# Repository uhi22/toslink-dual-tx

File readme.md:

# TOSLINK dual Transmitter

Converts two digital lines to optical (e.g. data and clock).

## Features

- allows inverting the clock signal
- optional chip select input for gating the clock
- if just straight-through signals are needed, omit the logic ICs and close the solder jumper for direct feed-through

## Specifications

- Optical transmitters: 2× Toshiba TOTX173 (6 Mb/s max)
- Supply: 8–18V, on-board L7805 5V regulator
- Logic: 74HC86 (clock invert), 74HC00 (clock gating via CS)

Made with KiCad version 9.

[Schematic (PDF)](toslink_dual_tx.pdf)

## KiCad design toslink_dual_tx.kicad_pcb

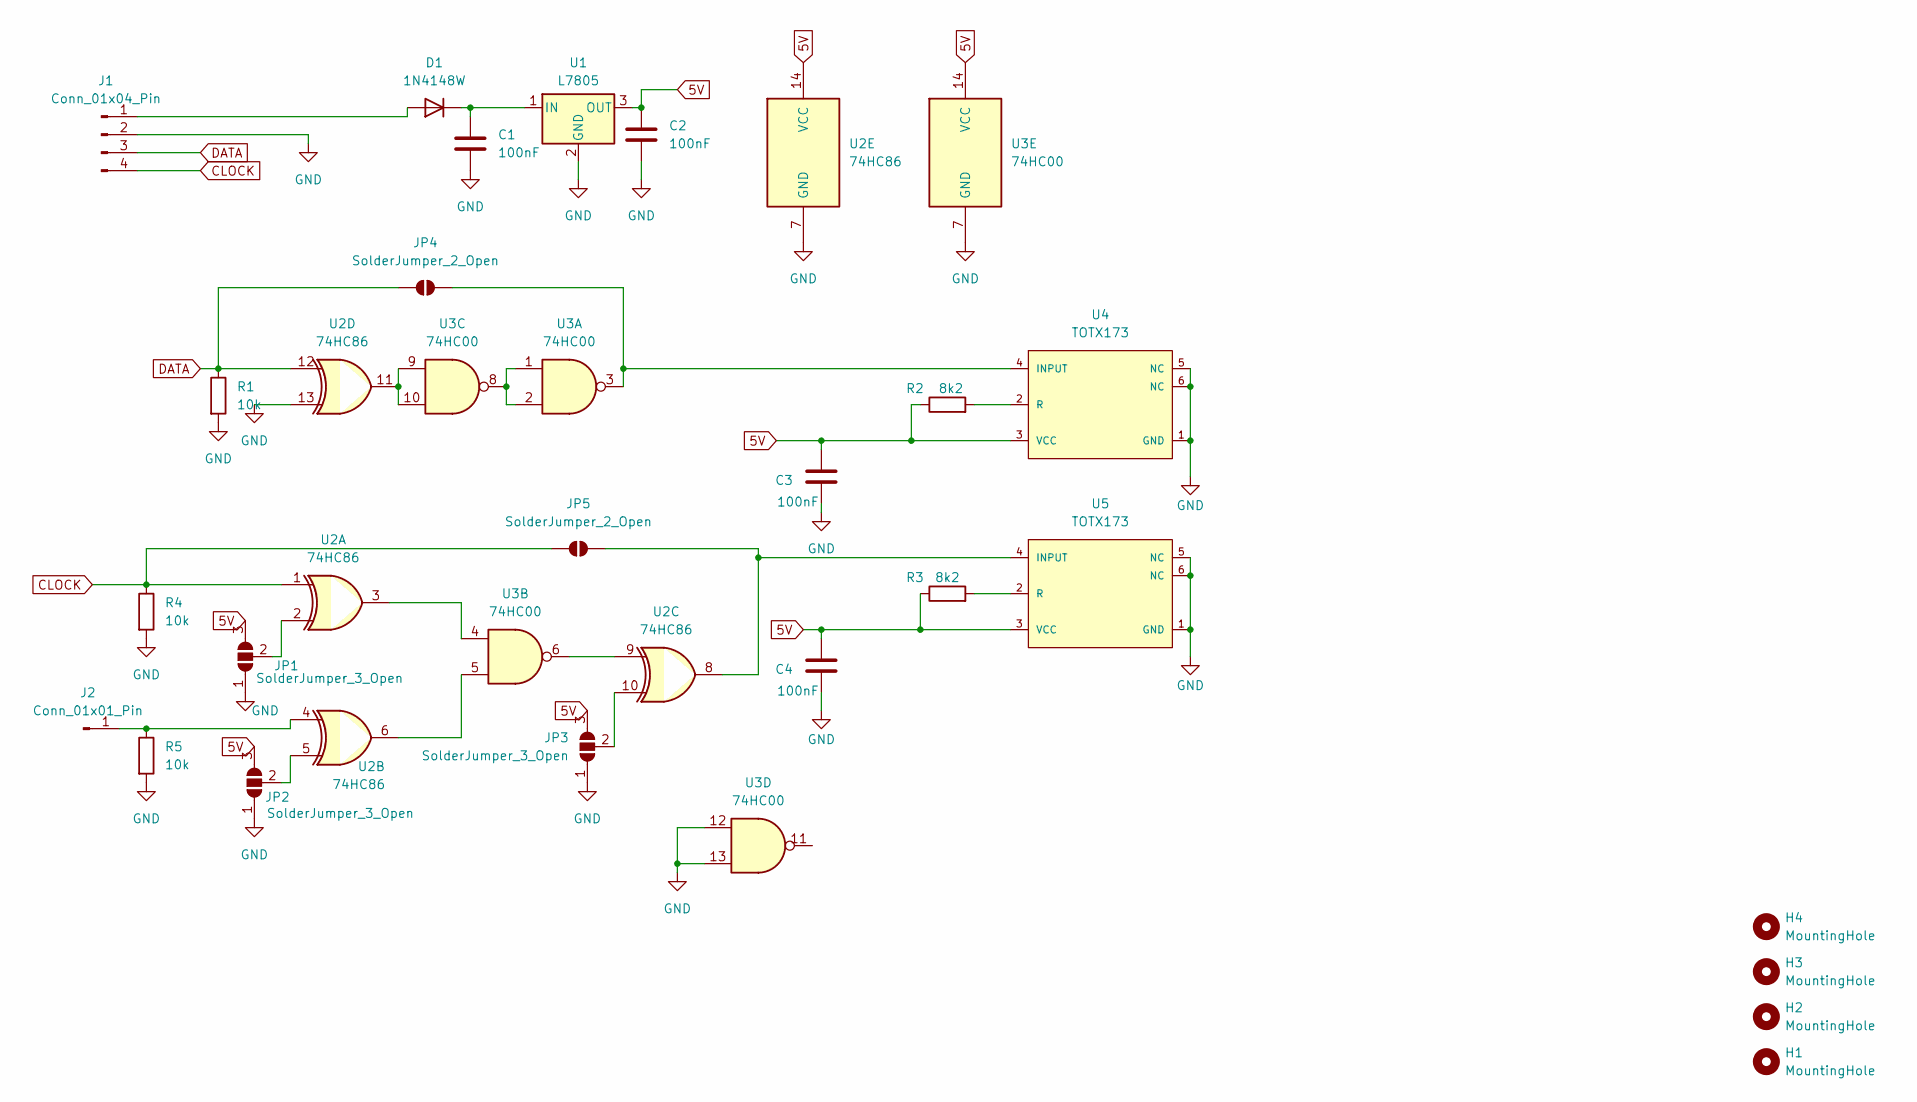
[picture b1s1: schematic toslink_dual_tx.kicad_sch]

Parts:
C1, C2, C3, C4: 100nF; C_0805_2012Metric_Pad1.18x1.45mm_HandSolder
D1: 1N4148W; D_SOD-123
H1, H2, H3, H4: MountingHole; MountingHole_3.2mm_M3
J1: Conn_01x04_Pin; PinHeader_1x04_P2.54mm_Vertical
J2: Conn_01x01_Pin; PinHeader_1x01_P2.54mm_Vertical
JP1, JP2, JP3: SolderJumper_3_Open; SolderJumper-3_P1.3mm_Open_RoundedPad1.0x1.5mm_NumberLabels
JP4, JP5: SolderJumper_2_Open; SolderJumper-2_P1.3mm_Open_Pad1.0x1.5mm
R1, R4, R5: 10k; R_0805_2012Metric_Pad1.20x1.40mm_HandSolder
R2, R3: 8k2; R_0805_2012Metric_Pad1.20x1.40mm_HandSolder
U1: L7805; TO-252-2
U2: 74HC86; SO-14_5.3x10.2mm_P1.27mm
U3: 74HC00; SO-14_5.3x10.2mm_P1.27mm
U4, U5: TOTX173; Toshiba_TOTX170_TOTX173_TOTX193_TOTX194

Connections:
5V: C2.1, C3.1, C4.1, JP1.3 (B), JP2.3 (B), JP3.3 (B), R2.1, R3.1, U1.3 (OUT), U2.14 (VCC), U3.14 (VCC), U4.3 (VCC), U5.3 (VCC)
CLOCK: J1.4, JP5.1 (A), R4.1, U2.1
DATA: J1.3, JP4.1 (A), R1.1, U2.12
GND: C1.2, C2.2, C3.2, C4.2, J1.2, JP1.1 (A), JP2.1 (A), JP3.1 (A), R1.2, R4.2, R5.2, U1.2 (GND), U2.7 (GND), U2.13, U3.7 (GND), U3.12, U3.13, U4.1 (GND), U4.5 (NC), U4.6 (NC), U5.1 (GND), U5.5 (NC), U5.6 (NC)
unnamed: D1.2 (A), J1.1
unnamed: C1.1, D1.1 (K), U1.1 (IN)
unnamed: J2.1, R5.1, U2.4
unnamed: JP1.2 (C), U2.2
unnamed: JP2.2 (C), U2.5
unnamed: JP3.2 (C), U2.10
unnamed: JP4.2 (B), U3.3, U4.4 (INPUT)
unnamed: JP5.2 (B), U2.8, U5.4 (INPUT)
unnamed: U2.3, U3.4
unnamed: U2.6, U3.5
unnamed: U2.9, U3.6
unnamed: U2.11, U3.9, U3.10
unnamed: U3.1, U3.2, U3.8
unnamed: R2.2, U4.2 (R)
unnamed: R3.2, U5.2 (R)

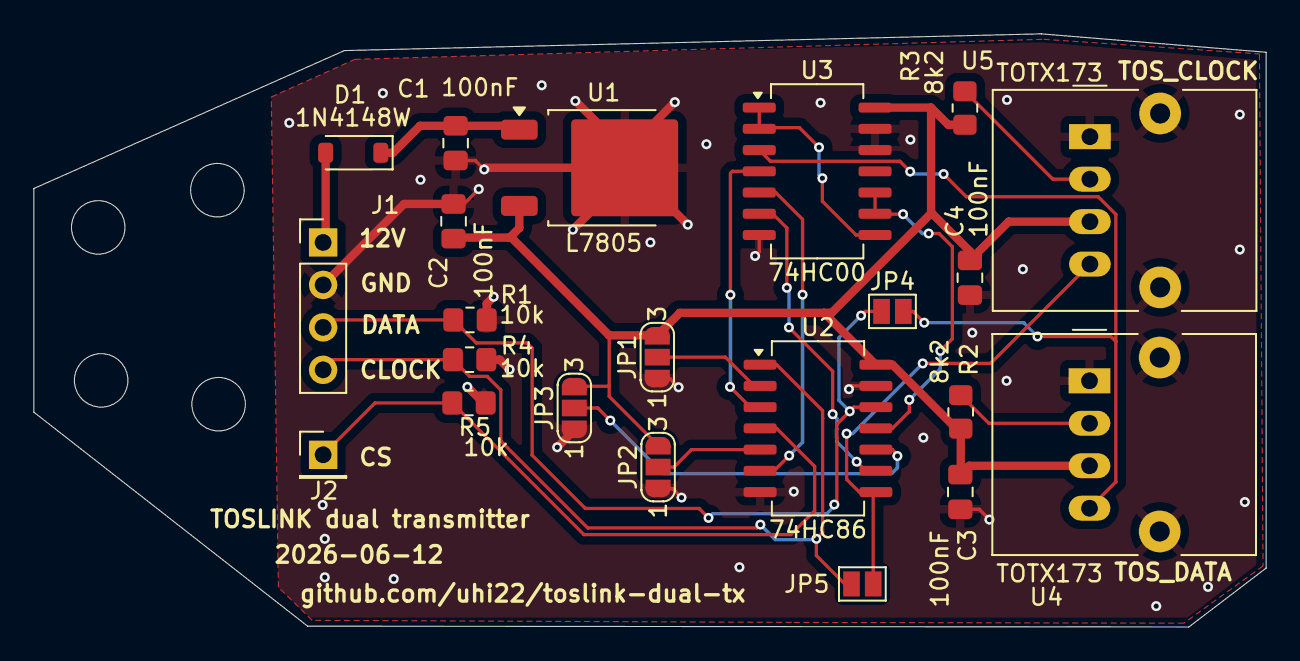
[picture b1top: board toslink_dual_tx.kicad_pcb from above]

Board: 2 copper layers, 73.7 x 35.5 mm, 26 parts (0 on the bottom side), 19 nets.

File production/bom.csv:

Designator,Footprint,Quantity,Value,LCSC Part #
"C1, C2, C3, C4",0805,4,100nF,
D1,D_SOD-123,1,1N4148W,
J1,PinHeader_1x04_P2.54mm_Vertical,1,Conn_01x04_Pin,
J2,PinHeader_1x01_P2.54mm_Vertical,1,Conn_01x01_Pin,
"R1, R4, R5",0805,3,10k,
"R2, R3",0805,2,8k2,
U1,TO-252-2,1,L7805,
U2,SO-14_5.3x10.2mm_P1.27mm,1,74HC86,
U3,SO-14_5.3x10.2mm_P1.27mm,1,74HC00,
"U4, U5",Toshiba_TOTX170_TOTX173_TOTX193_TOTX194,2,TOTX173,

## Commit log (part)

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2026-06-10 changed from DIL to SO-14 ICs
2026-06-11 added TOTX173 symbols and footprints
2026-06-11 fix DRC warnings
2026-06-12 added mounting holes, shrink size, added jumpers to bridge the logic gates
2026-06-12 added date on silkscreen, optimized holes
